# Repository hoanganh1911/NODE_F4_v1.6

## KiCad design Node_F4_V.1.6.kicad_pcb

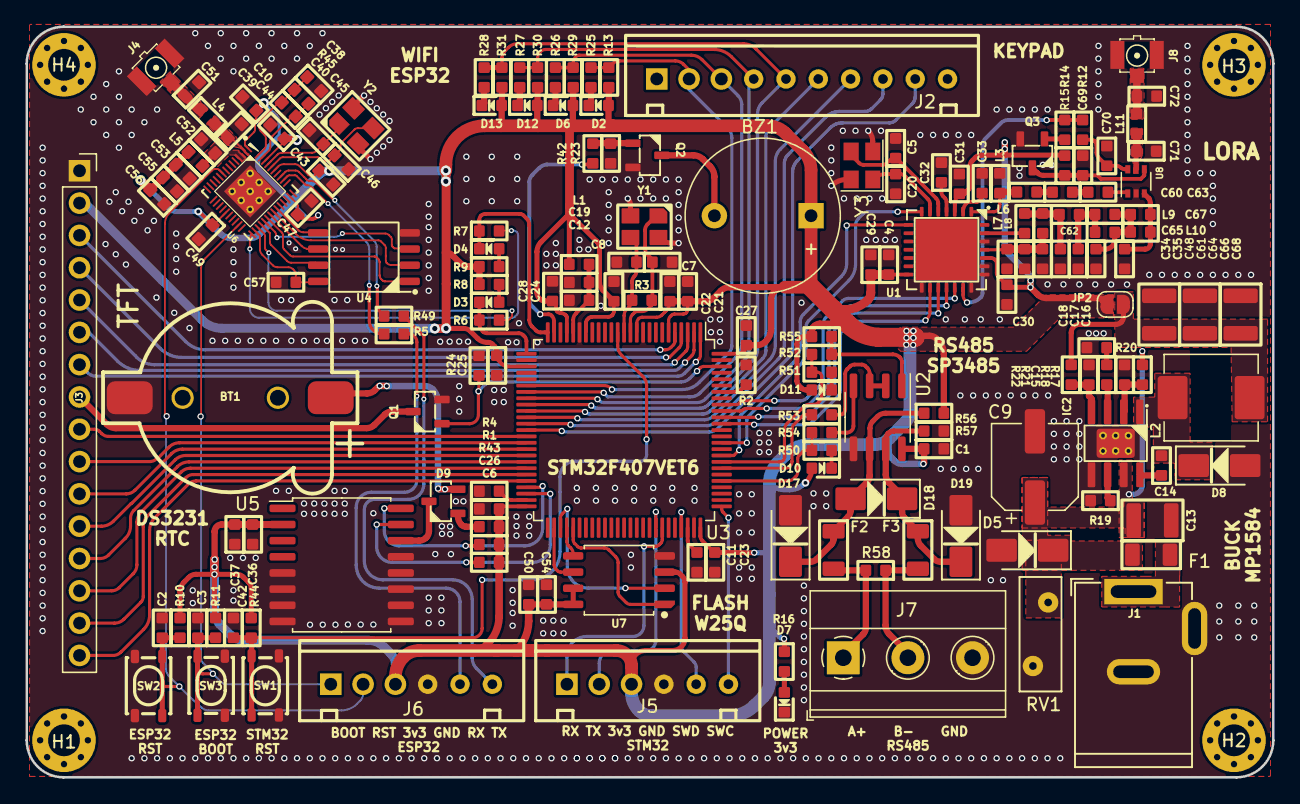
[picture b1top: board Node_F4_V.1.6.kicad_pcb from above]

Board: 2 copper layers, 98.0 x 59.0 mm, 178 parts (1 on the bottom side), 127 nets.

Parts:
BT1: Battery_Cell; BatteryHolder_CR1220
BZ1: Buzzer; Buzzer_12x9.5RM7.6
C1, C10, C14, C19, C21, C22, C23, C24, C25, C26, C27, C28, C29, C30, C31, C32, C33, C52, C53: 100nF; C_0603
C2, C36, C42, C50: 1u; C_0603
C3, C34, C38: 10nF; C_0603
C4, C44, C55, C57: 1uF; C_0603
C5, C20, C35, C66: 10pF; C_0603
C6, C11: 2.2uF; C_0603
C7, C8: 22pF; C_0603
C9: 100uF; CP_Elec_6.3x5.4
C12, C56: 10uF; C_0603
C13: 100nF; C_1210
C15: 220pF; C_0603
C16, C17, C18: 10uF; C_1210
C37, C54: 100n; C_0603
C39, C51, C71, C72: NC; C_0603
C40: 3.3nF; C_0603
C43, C69, C70: 100pF; C_0603
C45, C46, C64: 15pF; C_0603
C47, C49: 0.1uF; C_0603
C48, C60, C63: 47pF; C_0603
C61: 1.2pF; C_0603
C62: 1nF; C_0603
C65: 1.5pF; C_0603
C67: 3.3pF; C_0603
C68: 6.8pF; C_0603
D2, D3, D4, D6, D7, D12, D13: LED; LED_0603
D5, D8: SS34; D_SMA
D9: BAT54C; SOT23-3
D10: RS_Tx; LED_0603
D11: RS_Rx; LED_0603
D17, D18, D19: D_TVS; D_SMA
F1: Fuse_VCC; F_1206
F2, F3: Fuse; F_1206
G1: LOGO; MU_Footprint
H1, H2, H3, H4: MountingHole; MountingHole_2.5mm_Pad_Via
IC2: MP1584EN; SOIC-8_PAD_VIAS
J1: Conn_Jack-DC; DC_PowerJack_5mm_THT
J2: Conn_01x10; XH 2.54 10Pin Female
J3: Conn_01x16_Female; PinSocket_1x16_P2.54mm_Vertical
J4: RF_IPEX_U.FL-R-SMT; IPEX_Antena_Connector
J5: SWD; XH 2.54 6Pin Female
J6: WiFi_Prog; XH 2.54 6Pin Female
J7: RS485; TerminalBlock_Phoenix_MKDS-1,5-3-5.08_1x03_P5.08mm_Horizont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
J8: LoRa_Anten; IPEX_Antena_Connector
JP2: 3V3_EN; SolderJumper-2_P1.3mm_Open_RoundedPad1.0x1.5mm
L1: 2.2uH; L_0603
L2: 10uH; L_Abracon_ASPI-0630LR
L3, L6: 18nH; L_0603
L4, L5: 2.2nH; L_0603
L7: 4.3nH; L_0603
L8: 47nH; L_0603
L9, L11: 12nH; L_0603
L10: 10nH; L_0603
Q1: P_Mosfet; SOT23-3
Q2: MMBT3904L; SOT23-3
Q3: BC847; SOT23-3
R1, R4, R11, R55, R56, R57: 4k7; R_0603
R2, R13, R14, R29, R30, R31, R43: 1k; R_0603
R3: 2M; R_0603
R5, R49: 499; R_0603
R6, R7, R50, R51, R52, R53, R54: 100; R_0603
R8, R9: 100R; R_0603
R10, R12, R44: 10k; R_0603
R15, R24: 1M; R_0603
R16, R25, R26, R27, R28: 220; R_0603
R17, R18, R19, R20: 100k; R_0603
R21: 22k; R_0603
R22: 68k; R_0603
R23: 10K; R_0603
R42: 1K; R_0603
R45: 20k; R_0603
R58: 120; R_0603
RV1: Varistor; RV_Disc_D9mm_W3.3mm_P5mm
SW1, SW2, SW3: SW_Push; SW_SPST_PTS810
U1: SX1278; QFN-28_6x6_PAD
U2: SP3485EN; SOIC-8_3.9x4.9mm_P1.27mm
U3: STM32F407VETx; LQFP-100_14x14mm_P0.5mm
U4: Flash_W25Q128; SOIC-8_5.23x5.23
U5: DS3231M; SOIC-16W_7.5x10.3mm_P1.27mm
U6: ESP32-D0WD-V3; QFN-48-5x5_PAD-VIAS
U7: W25Q128JVS; SOIC-8_5.23x5.23mm_P1.27mm
U8: MASWSS0192; SOT-363_SC-70-6
Y1: 8MHz; Crystal_3225_4P_1-4
Y2: 40MHz; Crystal_3225_4P_1-4
Y3: 32MHz; Crystal_SMD_3225-4Pin_3.2x2.5mm

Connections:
+3.3V: BZ1.1 (-), C1.1, C4.1, C10.1, C21.1, C22.1, C23.1, C24.1, C25.1, C26.1, C27.1, C28.1, C29.1, C30.1, C31.1, C36.2, C37.2, C43.1, C44.1, C47.2, C49.1, C50.2, C53.2, C54.2, C55.2, C56.2, D2.2 (A), D6.2 (A), D10.2 (A), D11.2 (A), D12.2 (A), D13.2 (A), J3.2, J5.3, J6.3, JP2.2 (B), L1.1, L5.1, R1.2, R4.2, R8.2, R9.2, R10.1, R11.2, R13.1, R15.2, R16.1, R29.1, R30.1, R31.1, R43.1, R44.1, R55.2, R56.2, U1.3 (VBAT_ANA), U1.14 (VBAT_DIG), U1.24 (VBAT_RF), U2.8 (VCC), U3.6 (VBAT), U3.11 (VDD), U3.19 (VDD), U3.22 (VDDA), U3.28 (VDD), U3.50 (VDD), U3.75 (VDD), U3.100 (VDD), U5.2 (VCC), U6.1 (VDDA), U6.19 (VDD_RTC), U6.37 (VDD_CPU), U6.43 (VDDA), U6.46 (VDDA), U7.3 (IO2), U7.7 (IO3), U7.8 (VCC)
/A+: F2.2, J7.1, R58.2
/B-: F3.2, J7.2, R58.1
/BUZZER: R42.2, U3.24 (PA1)
/C1: J2.2, R13.2, R25.2, U3.31 (PA6)
/C2: J2.3, R26.2, R29.2, U3.32 (PA7)
/C3: J2.4, R27.2, R30.2, U3.33 (PC4)
/C4: J2.5, R28.2, R31.2, U3.34 (PC5)
/ESP_BOOT: C3.1, J6.1, R11.1, SW3.1, U6.23 (GPIO0)
/ESP_RST: C2.2, J6.2, R10.2, SW2.2, U6.9 (CHIP_PU)
/ESP_RX: D4.1 (K), R7.1, U3.25 (PA2)
/ESP_RX_LOAD: J6.5, R5.1
/ESP_TX: D3.1 (K), R6.2, U3.26 (PA3)
/ESP_TX_LOAD: J6.6, R49.1
/H1: J2.6, U3.35 (PB0)
/H2: J2.7, U3.36 (PB1)
/H3: J2.8, U3.37 (PB2)
/H4: J2.9, U3.38 (PE7)
/I2C_SCL: R1.1, U3.47 (PB10), U5.16 (SCL)
/I2C_SDA: R4.1, U3.48 (PB11), U5.15 (SDA)
/LORA NSS: U1.19 (NSS), U3.92 (PB6)
/LORA_INT: U1.8 (DIO0), U3.84 (PD3)
/LORA_RST: U1.7 (~RESET), U3.86 (PD5)
/RS485_DERE: R53.1, U3.82 (PD1)
/RS485_DI: R50.1, R54.1, U3.80 (PC12)
/RS485_RO: R51.1, R52.1, U3.83 (PD2)
/SCK_CLK: U4.6 (CLK), U6.31 (SD_CLK)
/SCS_CMD: U4.1 (~CS), U6.30 (SD_CMD)
/SDI_SD1: U4.5 (DI(IO0)), U6.33 (SD_D1)
/SDO_SD0: U4.2 (DO(IO1)), U6.32 (SD_D0)
/SHD_SD2: U4.7 (IO3), U6.28 (SD_D2)
/SPI2_MISO: U3.53 (PB14), U7.2 (DO(IO1))
/SPI2_MOSI: U3.54 (PB15), U7.5 (DI(IO0))
/SPI2_SCK: U3.52 (PB13), U7.6 (CLK)
/SPI3_MISO: U1.17 (MISO), U3.90 (PB4)
/SPI3_MOSI: U1.18 (MOSI), U3.91 (PB5)
/SPI3_SCK: U1.16 (SCK), U3.89 (PB3)
/SWCLK: J5.6, U3.76 (PA14)
/SWDIO: J5.5, U3.72 (PA13)
/SWP_SD3: U4.3 (IO2), U6.29 (SD_D3)
/TFT_CS: J3.3, U3.5 (PE6)
/TFT_DB0: J3.9, U3.39 (PE8)
/TFT_DB1: J3.10, U3.40 (PE9)
/TFT_DB2: J3.11, U3.41 (PE10)
/TFT_DB3: J3.12, U3.42 (PE11)
/TFT_DB4: J3.13, U3.43 (PE12)
/TFT_DB5: J3.14, U3.44 (PE13)
/TFT_DB6: J3.15, U3.45 (PE14)
/TFT_DB7: J3.16, U3.46 (PE15)
/TFT_LED: Q1.1 (G), R24.2, U3.98 (PE1)
/TFT_RD: J3.6, U3.2 (PE3)
/TFT_RS: J3.4, U3.4 (PE5)
/TFT_RST: J3.7, U3.1 (PE2)
/TFT_WR: J3.5, U3.3 (PE4)
/UART_RX_LOG: J5.1, U3.69 (PA10)
/UART_TX_LOG: J5.2, U3.68 (PA9)
/W25Q_CS: U3.55 (PD8), U7.1 (~CS)
GND: BT1.2 (-), C1.2, C2.1, C3.2, C4.2, C5.1, C6.2, C7.2, C8.2, C9.2, C10.2, C11.2, C12.2, C13.1, C16.1, C17.1, C18.1, C19.1, C20.1, C21.2, C22.2, C23.2, C24.2, C25.2, C26.2, C27.2, C28.2, C29.2, C30.2, C31.2, C32.2, C33.2, C34.2, C35.2, C36.1, C37.1, C38.2, C39.2, C42.1, C43.2, C44.2, C45.1, C46.1, C47.1, C48.2, C49.2, C50.1, C51.2, C52.1, C53.1, C54.1, C55.1, C56.1, C57.1, C61.2, C64.1, C66.1, C68.1, C69.1, C70.1, C71.1, C72.1, D5.2 (A), D7.1 (K), D8.2 (A), D17.2 (A2), D19.2 (A2), IC2.5 (GND), IC2.9 (EP), J1.2, J1.3, J3.1, J4.2 (Ext), J5.4, J6.4, J7.3, J8.2 (Ext), L3.2, Q1.2 (S), Q2.2 (E), Q3.2 (E), R2.2, R18.2, R19.2, R20.2, R21.2, R23.2, R24.1, R57.1, RV1.2, SW1.1, SW2.1, SW3.2, U1.15 (GND), U1.21 (GND), U1.22 (GND), U1.23 (GND), U1.26 (GND), U1.29 (GND), U2.5 (GND), U3.10 (VSS), U3.20 (VSSA), U3.27 (VSS), U3.74 (VSS), U3.99 (VSS), U4.4 (GND), U5.5 (GND), U5.6 (GND), U5.7 (GND), U5.8 (GND), U5.9 (GND), U5.10 (GND), U5.11 (GND), U5.12 (GND), U5.13 (GND), U6.49 (GND_PAD), U7.4 (GND), U8.2 (GND), Y1.2, Y1.4, Y2.2, Y2.4, Y3.2, Y3.4
unnamed: BT1.1 (+), D9.2
unnamed: BZ1.2 (+), Q2.3 (C)
unnamed: C15.1, R20.1
unnamed: C52.2, L5.2, U6.3 (VDD), U6.4 (VDD)
unnamed: C60.1, L6.2
unnamed: C60.2, C63.1
unnamed: C61.1, C62.1, L7.2, L8.1
unnamed: C62.2, C64.2, C65.1, L9.1
unnamed: C65.2, C66.2, C67.1, L9.2, L10.1
unnamed: D2.1 (K), R25.1
unnamed: D3.2 (A), R8.1
unnamed: D4.2 (A), R9.1
unnamed: D6.1 (K), R26.1
unnamed: D7.2 (A), R16.2
unnamed: C14.2, D8.1 (K), IC2.1 (SW), L2.1
unnamed: D9.1, R43.2
unnamed: D10.1 (K), R50.2
unnamed: D11.1 (K), R51.2
unnamed: D12.1 (K), R27.1
unnamed: D13.1 (K), R28.1
unnamed: D17.1 (A1), D18.2 (A2), F2.1, R56.1, U2.6 (A)
unnamed: D18.1 (A1), D19.1 (A1), F3.1, R57.2, U2.7 (B)
unnamed: F1.1, J1.1
unnamed: C14.1, IC2.8 (BST)
unnamed: C15.2, IC2.3 (COMP)
unnamed: IC2.2 (EN), R17.2, R18.1
unnamed: IC2.4 (FB), R21.1, R22.1
unnamed: IC2.6 (FREQ), R19.1
unnamed: J3.8, Q1.3 (D)
unnamed: C51.1, J4.1 (In), L4.1
unnamed: C72.2, J8.1 (In), L11.2
unnamed: C16.2, C17.2, C18.2, JP2.1 (A), L2.2, R22.2
unnamed: Q2.1 (B), R23.1, R42.1
unnamed: Q3.1 (B), R14.2
unnamed: C69.2, Q3.3 (C), R15.1, U8.4 (V2)
unnamed: L7.1, U1.27 (PA_BOOST)
unnamed: L3.1, L6.1, U1.1 (RFI_LF)
unnamed: R12.1, R14.1, U1.20 (RXTX/RF_MOD)
unnamed: C33.1, U1.2 (VR_ANA)
unnamed: C32.1, U1.4 (VR_DIG)
unnamed: C34.1, C35.1, C48.1, L8.2, U1.25 (VR_PA)
unnamed: C5.2, U1.5 (XTA), Y3.3
unnamed: C20.2, U1.6 (XTB), Y3.1
unnamed: R53.2, U2.2 (~RE), U2.3 (DE)
unnamed: R54.2, U2.4 (DI)
unnamed: R52.2, R55.1, U2.1 (RO)
unnamed: R2.1, U3.94 (BOOT0)
unnamed: C42.2, R44.2, SW1.2, U3.14 (NRST)
unnamed: C7.1, R3.2, U3.12 (PH0), Y1.1
unnamed: C8.1, R3.1, U3.13 (PH1), Y1.3
unnamed: C6.1, U3.49 (VCAP_1)
unnamed: C11.1, U3.73 (VCAP_2)
unnamed: C12.1, C19.2, L1.2, U3.21 (VREF+)
unnamed: C57.2, U4.8 (VCC), U6.26 (VDD_SDIO)
unnamed: D9.3, U5.14 (VBAT)
unnamed: C38.1, C40.2, R45.2, U6.48 (CAP1)
unnamed: C40.1, R45.1, U6.47 (CAP2)
unnamed: R7.2, U6.25 (GPIO16)
unnamed: R6.1, U6.27 (GPIO17)
unnamed: C39.1, L4.2, U6.2 (LNA_IN)
unnamed: R5.2, U6.40 (U0RXD)
unnamed: R49.2, U6.41 (U0TXD)
unnamed: C46.2, U6.44 (XTAL_N), Y2.3
unnamed: C45.2, U6.45 (XTAL_P), Y2.1
unnamed: C63.2, U8.1 (RF1)
unnamed: C67.2, C68.2, L10.2, U8.3 (RF2)
unnamed: C71.2, L11.1, U8.5 (RFC)
unnamed: C70.2, R12.2, U8.6 (V1)
VCC: C9.1, C13.2, D5.1 (K), F1.2, IC2.7 (VIN), R17.1, RV1.1

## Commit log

2023-03-31 add gitignore
2023-03-31 DI track
2023-04-02 Xep linh kien
2023-04-04 Layout gan xong
2023-04-05 Via not foundand connect GND
2023-04-06 Xong layout cho var
2023-04-06 Add via tranh cuon cam va lora
2023-04-06 Layout nguon
2023-04-06 Sua day cong
2023-04-07 Layout flash ESP32
2023-04-07 LAYOUT OK check schematic again
2023-04-07 Waitting ...

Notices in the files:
parts and their libraries:
Copyright 2021 Accelerated Designs. All rights reserved.
